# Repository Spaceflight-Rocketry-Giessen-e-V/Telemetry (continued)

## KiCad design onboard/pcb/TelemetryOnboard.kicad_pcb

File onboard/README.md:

# The Onboard System

- [Electronics Hardware](/onboard/pcb/)
    - [KiCad Design Files](/onboard/pcb/)
    - [PDF Schematic](/onboard/pcb/TelemetryOnboard_Schematic.pdf)
    - [Interactive Schematic / iBOM](/onboard/pcb/TelemetryOnboard_iBOM.html)
    - [BOM](/onboard/pcb/TelemetryOnboard_BOM.csv)
    - [Gerber Files](/onboard/pcb/Production%20Files/)
    - [PCB 3D Model](/onboard/pcb/TelemetryOnboard.step)
    - [PCB Images](/onboard/pcb/images/)
- [Mounting Structure](/onboard/mounting%20structure/)
- [Firmware](/onboard/firmware/)
- [869 MHz QFH Antenna](/onboard/antenna/) (not yet available)

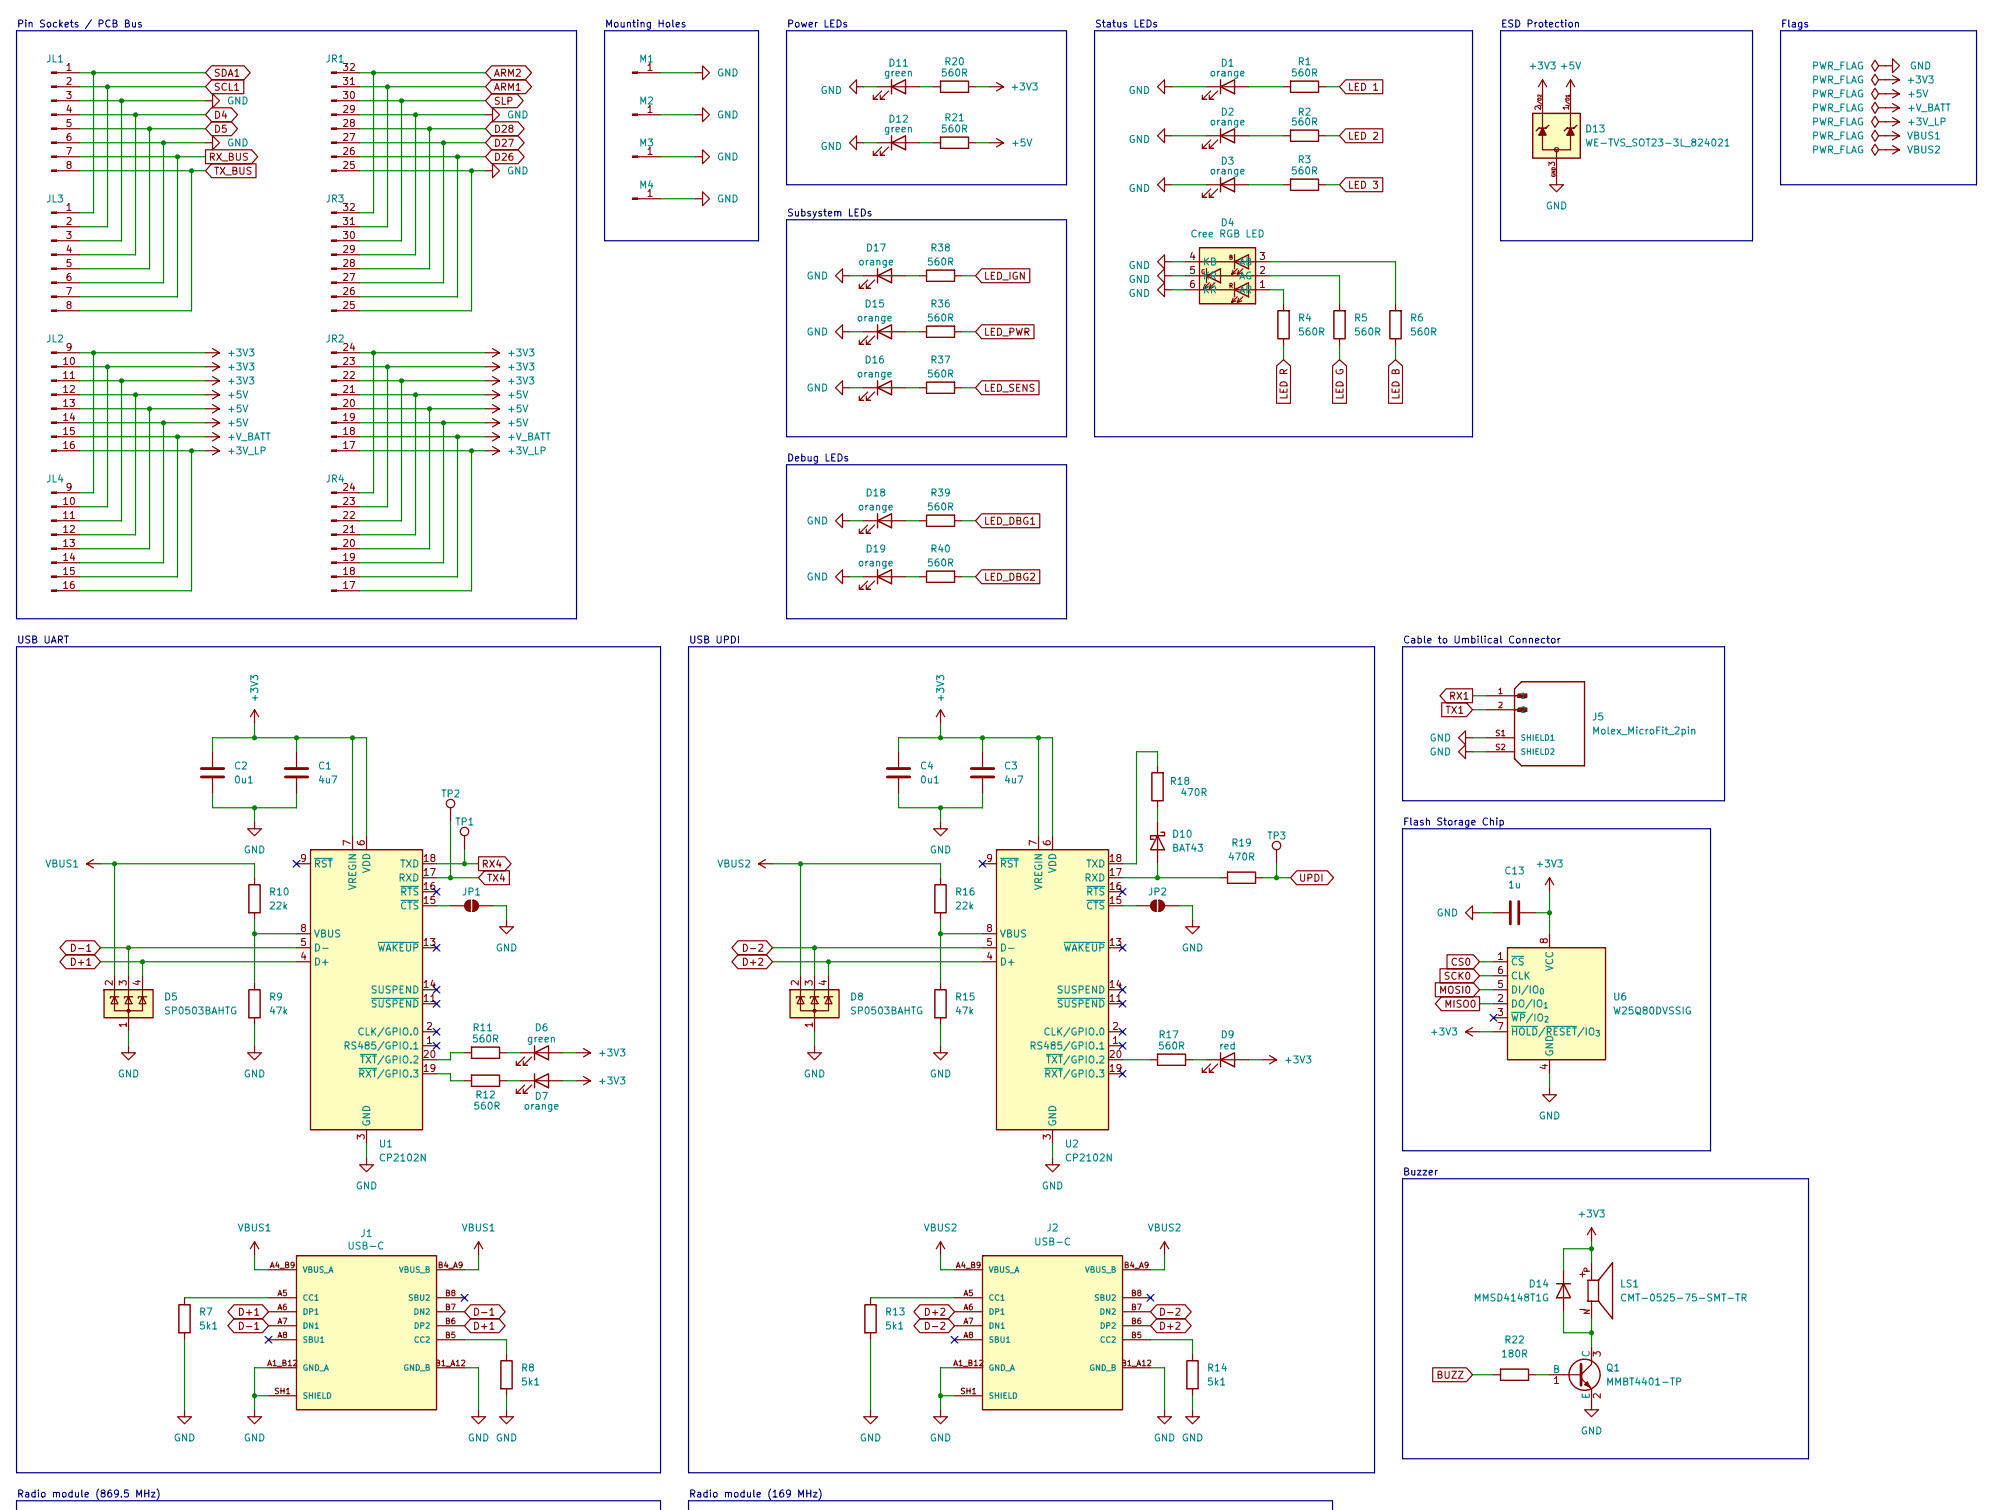
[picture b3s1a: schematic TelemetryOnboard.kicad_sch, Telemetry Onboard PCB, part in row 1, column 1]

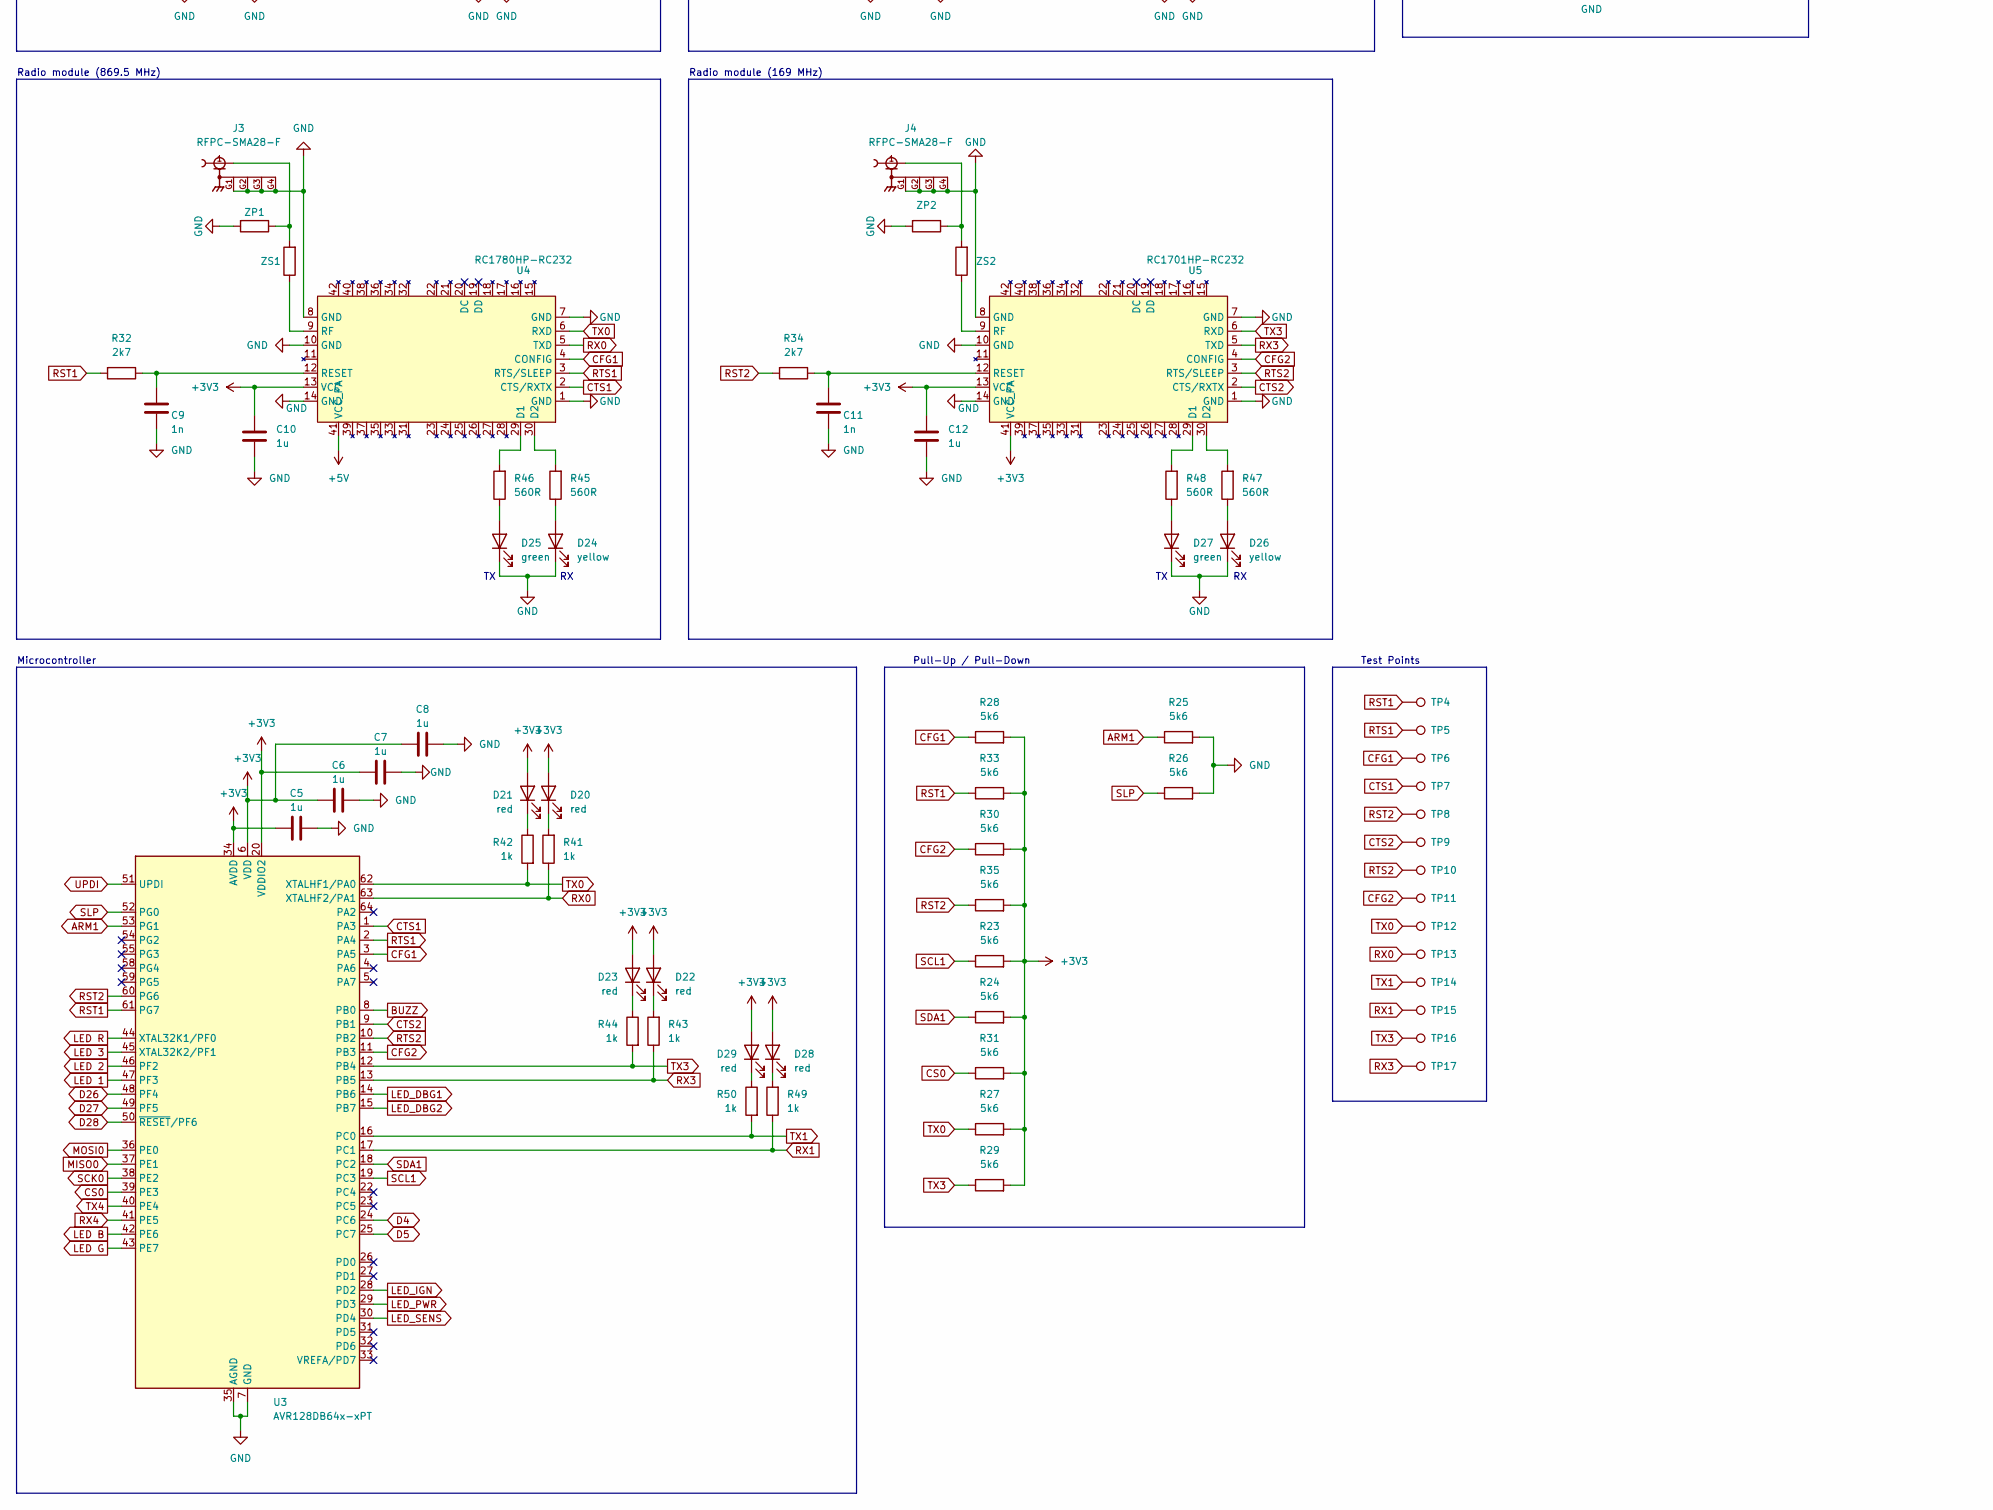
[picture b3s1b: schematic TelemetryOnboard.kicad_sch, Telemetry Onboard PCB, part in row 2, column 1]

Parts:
C1, C3: 4u7; C_0805_2012Metric_Pad1.18x1.45mm_HandSolder
C2, C4: 0u1; C_0805_2012Metric_Pad1.18x1.45mm_HandSolder
C5, C6, C7, C8, C10, C12, C13: 1u; C_0805_2012Metric_Pad1.18x1.45mm_HandSolder
C9, C11: 1n; C_0805_2012Metric_Pad1.18x1.45mm_HandSolder
D1, D2, D3, D7, D15, D16, D17, D18, D19: orange; LED_0805_2012Metric_Pad1.15x1.40mm_HandSolder
D4: Cree RGB LED
D5, D8: SP0503BAHTG; SOT-143
D6, D11, D12, D25, D27: green; LED_0805_2012Metric_Pad1.15x1.40mm_HandSolder
D9, D20, D21, D22, D23, D28, D29: red; LED_0805_2012Metric_Pad1.15x1.40mm_HandSolder
D10: BAT43; D_SOD-123
D13: WE-TVS_SOT23-3L_824021; SOT-23-3
D14: MMSD4148T1G; D_SOD-123
D24, D26: yellow; LED_0805_2012Metric_Pad1.15x1.40mm_HandSolder
J1, J2: USB-C; GCT_USB4216-03-A_REVA; PARTREV A; DigiKey_Part_Number 2073-USB4215-03-ACT-ND
J3, J4: RFPC-SMA28-F; PARTREV 1.0; DigiKey_Part_Number 2073-RFPC-SMA28-F-ND
J5: Molex_MicroFit_2pin; PARTREV F3; DigiKey_Part_Number WM1870-ND
JL1: Stackable Socket 1x8; JL1
JL2: Stackable Socket 1x8; JL2
JL3: Stackable Socket 1x8; JL3
JL4: Stackable Socket 1x8; JL4
JP1, JP2: SolderJumper_2_Open; Solder Jumper
JR1: Stackable Socket 1x8; JR1
JR2: Stackable Socket 1x8; JR2
JR3: Stackable Socket 1x8; JR3
JR4: Stackable Socket 1x8; JR4
LS1: CMT-0525-75-SMT-TR; Buzzer XDCR_CMT-0525-75-SMT-TR; PARTREV 1.0
M1, M2, M3, M4: M4 Mounting Hole
Q1: MMBT4401-TP; SOT-23
R1, R2, R3, R4, R5, R6, R11, R12, R17, R20, R21, R36, R37, R38, R39, R40, R45, R46, R47, R48: 560R; R_0805_2012Metric_Pad1.20x1.40mm_HandSolder
R7, R8, R13, R14: 5k1; R_0805_2012Metric_Pad1.20x1.40mm_HandSolder
R9, R15: 47k; R_0805_2012Metric_Pad1.20x1.40mm_HandSolder
R10, R16: 22k; R_0805_2012Metric_Pad1.20x1.40mm_HandSolder
R18, R19: 470R; R_0805_2012Metric_Pad1.20x1.40mm_HandSolder
R22: 180R; R_0805_2012Metric_Pad1.20x1.40mm_HandSolder
R23, R24, R25, R26, R27, R28, R29, R30, R31, R33, R35: 5k6; R_0805_2012Metric_Pad1.20x1.40mm_HandSolder
R32, R34: 2k7; R_0805_2012Metric_Pad1.20x1.40mm_HandSolder
R41, R42, R43, R44, R49, R50: 1k; R_0805_2012Metric_Pad1.20x1.40mm_HandSolder
TP1, TP2, TP3, TP4, TP5, TP6, TP7, TP8, TP9, TP10, TP11, TP12, TP13, TP14, TP15, TP16, TP17: TestPoint; Test Point
U1, U2: CP2102N; QFN20_CP2102N_SIL
U3: AVR128DB64x-xPT; TQFP-64_10x10mm_P0.5mm
U4: RC1780HP-RC232; Radiocrafts RC1780HP-RC232
U5: RC1701HP-RC232; Radiocrafts RC1780HP-RC232
U6: W25Q80DVSSIG; SOIC-8_5.3x5.3mm_P1.27mm
ZP1, ZP2: R_0805_2012Metric_Pad1.20x1.40mm_HandSolder
ZS1, ZS2: R_0805_2012Metric_Pad1.20x1.40mm_HandSolder

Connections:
+3V3: C1.1, C2.1, C3.1, C4.1, C5.1, C6.1, C7.2, C8.2, C10.1, C12.1, C13.2, D6.2 (A), D7.2 (A), D9.2 (A), D13.2, D14.1 (K), D20.2 (A), D21.2 (A), D22.2 (A), D23.2 (A), D28.2 (A), D29.2 (A), JL2.9 (Pin_1), JL2.10 (Pin_2), JL2.11 (Pin_3), JL4.9 (Pin_1), JL4.10 (Pin_2), JL4.11 (Pin_3), JR2.22 (26), JR2.23 (Pin_2), JR2.24 (Pin_1), JR4.22 (26), JR4.23 (Pin_2), JR4.24 (Pin_1), LS1.P, R20.1, R23.2, R24.2, R27.2, R28.2, R29.2, R30.2, R31.2, R33.2, R35.2, U1.6 (VDD), U1.7 (VREGIN), U2.6 (VDD), U2.7 (VREGIN), U3.6 (VDD), U3.20 (VDDIO2), U3.34 (AVDD), U3.56 (VDD), U4.13 (VCC), U5.13 (VCC), U5.41 (VCC_PA), U6.7 (~HOLD/~RESET/IO_{3}), U6.8 (VCC)
+3V_LP: JL2.16 (Pin_8), JL4.16 (Pin_8), JR2.17 (Pin_8), JR4.17 (Pin_8)
+5V: D13.1, JL2.12 (Pin_4), JL2.13 (Pin_5), JL2.14 (Pin_6), JL4.12 (Pin_4), JL4.13 (Pin_5), JL4.14 (Pin_6), JR2.19 (Pin_6), JR2.20 (Pin_5), JR2.21 (Pin_4), JR4.19 (Pin_6), JR4.20 (Pin_5), JR4.21 (Pin_4), R21.1, U4.41 (VCC_PA)
+V_BATT: JL2.15 (Pin_7), JL4.15 (Pin_7), JR2.18 (Pin_7), JR4.18 (Pin_7)
ARM1: JR1.31 (Pin_2), JR3.31 (Pin_2), R25.1, U3.53 (PG1)
ARM2: JR1.32 (Pin_1), JR3.32 (Pin_1)
BUZZ: R22.2, U3.8 (PB0)
CFG1: R28.1, TP6.1, U3.3 (PA5), U4.4 (CONFIG)
CFG2: R30.1, TP11.1, U3.11 (PB3), U5.4 (CONFIG)
CS0: R31.1, U3.39 (PE3), U6.1 (~CS)
CTS1: TP7.1, U3.1 (PA3), U4.2 (CTS/RXTX)
CTS2: TP9.1, U3.9 (PB1), U5.2 (CTS/RXTX)
D4: JL1.4, JL3.4, U3.24 (PC6)
D5: JL1.5, JL3.5, U3.25 (PC7)
D26: JR1.26 (Pin_7), JR3.26 (Pin_7), U3.48 (PF4)
D27: JR1.27 (Pin_6), JR3.27 (Pin_6), U3.49 (PF5)
D28: JR1.28 (Pin_5), JR3.28 (Pin_5), U3.50 (~RESET/PF6)
D+1: D5.4 (K), J1.A6 (DP1), J1.B6 (DP2), U1.4 (D+)
D+2: D8.4 (K), J2.A6 (DP1), J2.B6 (DP2), U2.4 (D+)
D-1: D5.3 (K), J1.A7 (DN1), J1.B7 (DN2), U1.5 (D-)
D-2: D8.3 (K), J2.A7 (DN1), J2.B7 (DN2), U2.5 (D-)
GND: C1.2, C2.2, C3.2, C4.2, C5.2, C6.2, C7.1, C8.1, C9.2, C10.2, C11.2, C12.2, C13.1, D1.1 (K), D2.1 (K), D3.1 (K), D4.4 (KB), D4.5 (KR), D4.6 (KR), D5.1 (A), D8.1 (A), D11.1 (K), D12.1 (K), D13.3, D15.1 (K), D16.1 (K), D17.1 (K), D18.1 (K), D19.1 (K), D24.1 (K), D25.1 (K), D26.1 (K), D27.1 (K), J1.A1_B12 (GND_A), J1.B1_A12 (GND_B), J1.SH1 (SHIELD), J1.SH2 (SHIELD), J1.SH3 (SHIELD), J1.SH4 (SHIELD), J2.A1_B12 (GND_A), J2.B1_A12 (GND_B), J2.SH1 (SHIELD), J2.SH2 (SHIELD), J2.SH3 (SHIELD), J2.SH4 (SHIELD), J3.G1, J3.G2, J3.G3, J3.G4, J4.G1, J4.G2, J4.G3, J4.G4, J5.S1 (SHIELD1), J5.S2 (SHIELD2), JL1.3, JL1.6, JL3.3, JL3.6, JP1.2 (B), JP2.2 (B), JR1.25 (Pin_8), JR1.29 (Pin_4), JR3.25 (Pin_8), JR3.29 (Pin_4), M1.1, M2.1, M3.1, M4.1, Q1.2 (E), R7.2, R8.2, R9.2, R13.2, R14.2, R15.2, R25.2, R26.2, U1.3 (GND), U1.12 (GND), U1.21 (GND), U2.3 (GND), U2.12 (GND), U2.21 (GND), U3.7 (GND), U3.21 (GND), U3.35 (AGND), U3.57 (GND), U4.1 (GND), U4.7 (GND), U4.8 (GND), U4.10 (GND), U4.14 (GND), U5.1 (GND), U5.7 (GND), U5.8 (GND), U5.10 (GND), U5.14 (GND), U6.4 (GND), ZP1.2, ZP2.2
LED 1: R1.1, U3.47 (PF3)
LED 2: R2.1, U3.46 (PF2)
LED 3: R3.1, U3.45 (XTAL32K2/PF1)
LED B: R6.1, U3.42 (PE6)
LED G: R5.1, U3.43 (PE7)
LED R: R4.1, U3.44 (XTAL32K1/PF0)
LED_DBG1: R39.2, U3.14 (PB6)
LED_DBG2: R40.2, U3.15 (PB7)
LED_IGN: R38.2, U3.28 (PD2)
LED_PWR: R36.2, U3.29 (PD3)
LED_SENS: R37.2, U3.30 (PD4)
MISO0: U3.37 (PE1), U6.2 (DO/IO_{1})
MOSI0: U3.36 (PE0), U6.5 (DI/IO_{0})
unnamed: D1.2 (A), R1.2
unnamed: D2.2 (A), R2.2
unnamed: D3.2 (A), R3.2
unnamed: D4.3 (AB), R6.2
unnamed: D4.2 (AG), R5.2
unnamed: D4.1 (AR), R4.2
unnamed: D6.1 (K), R11.1
unnamed: D7.1 (K), R12.1
unnamed: D9.1 (K), R17.1
unnamed: D10.2 (A), R19.2, U2.17 (RXD)
unnamed: D10.1 (K), R18.1
unnamed: D11.2 (A), R20.2
unnamed: D12.2 (A), R21.2
unnamed: D14.2 (A), LS1.N, Q1.3 (C)
unnamed: D15.2 (A), R36.1
unnamed: D16.2 (A), R37.1
unnamed: D17.2 (A), R38.1
unnamed: D18.2 (A), R39.1
unnamed: D19.2 (A), R40.1
unnamed: D20.1 (K), R41.2
unnamed: D21.1 (K), R42.1
unnamed: D22.1 (K), R43.2
unnamed: D23.1 (K), R44.1
unnamed: D24.2 (A), R45.1
unnamed: D25.2 (A), R46.1
unnamed: D26.2 (A), R47.1
unnamed: D27.2 (A), R48.1
unnamed: D28.1 (K), R49.2
unnamed: D29.1 (K), R50.1
unnamed: J1.A5 (CC1), R7.1
unnamed: J1.B5 (CC2), R8.1
unnamed: J2.A5 (CC1), R13.1
unnamed: J2.B5 (CC2), R14.1
unnamed: J3.1, ZP1.1, ZS1.2
unnamed: J4.1, ZP2.1, ZS2.2
unnamed: JP1.1 (A), U1.15 (~CTS)
unnamed: JP2.1 (A), U2.15 (~CTS)
unnamed: Q1.1 (B), R22.1
unnamed: R9.1, R10.2, U1.8 (VBUS)
unnamed: R12.2, U1.19 (~RXT/GPIO.3)
unnamed: R11.2, U1.20 (~TXT/GPIO.2)
unnamed: R18.2, U2.18 (TXD)
unnamed: R15.1, R16.2, U2.8 (VBUS)
unnamed: R17.2, U2.20 (~TXT/GPIO.2)
unnamed: R46.2, U4.29 (D1)
unnamed: R45.2, U4.30 (D2)
unnamed: C9.1, R32.1, U4.12 (RESET)
unnamed: U4.9 (RF), ZS1.1
unnamed: R48.2, U5.29 (D1)
unnamed: R47.2, U5.30 (D2)
unnamed: C11.1, R34.1, U5.12 (RESET)
unnamed: U5.9 (RF), ZS2.1
RST1: R32.2, R33.1, TP4.1, U3.61 (PG7)
RST2: R34.2, R35.1, TP8.1, U3.60 (PG6)
RTS1: TP5.1, U3.2 (PA4), U4.3 (RTS/SLEEP)
RTS2: TP10.1, U3.10 (PB2), U5.3 (RTS/SLEEP)
RX0: R41.1, TP13.1, U3.63 (XTALHF2/PA1), U4.5 (TXD)
RX1: J5.1, R49.1, TP15.1, U3.17 (PC1)
RX3: R43.1, TP17.1, U3.13 (PB5), U5.5 (TXD)
RX4: TP1.1, U1.18 (TXD), U3.41 (PE5)
RX_BUS: JL1.7, JL3.7
SCK0: U3.38 (PE2), U6.6 (CLK)
SCL1: JL1.2, JL3.2, R23.1, U3.19 (PC3)
SDA1: JL1.1, JL3.1, R24.1, U3.18 (PC2)
SLP: JR1.30 (26), JR3.30 (26), R26.1, U3.52 (PG0)
TX0: R27.1, R42.2, TP12.1, U3.62 (XTALHF1/PA0), U4.6 (RXD)
TX1: J5.2, R50.2, TP14.1, U3.16 (PC0)
TX3: R29.1, R44.2, TP16.1, U3.12 (PB4), U5.6 (RXD)
TX4: TP2.1, U1.17 (RXD), U3.40 (PE4)
TX_BUS: JL1.8, JL3.8
UPDI: R19.1, TP3.1, U3.51 (UPDI)
VBUS1: D5.2 (K), J1.A4_B9 (VBUS_A), J1.B4_A9 (VBUS_B), R10.1
VBUS2: D8.2 (K), J2.A4_B9 (VBUS_A), J2.B4_A9 (VBUS_B), R16.1

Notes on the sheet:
Subsystem LEDs
Pull-Up / Pull-Down
Pin Sockets / PCB Bus
Flash Storage Chip
Microcontroller
Radio module (169 MHz)
Flags
USB UPDI
Test Points
Buzzer
USB UART
Status LEDs
Debug LEDs
Mounting Holes
Power LEDs
ESD Protection
Radio module (869.5 MHz)
Cable to Umbilical Connector

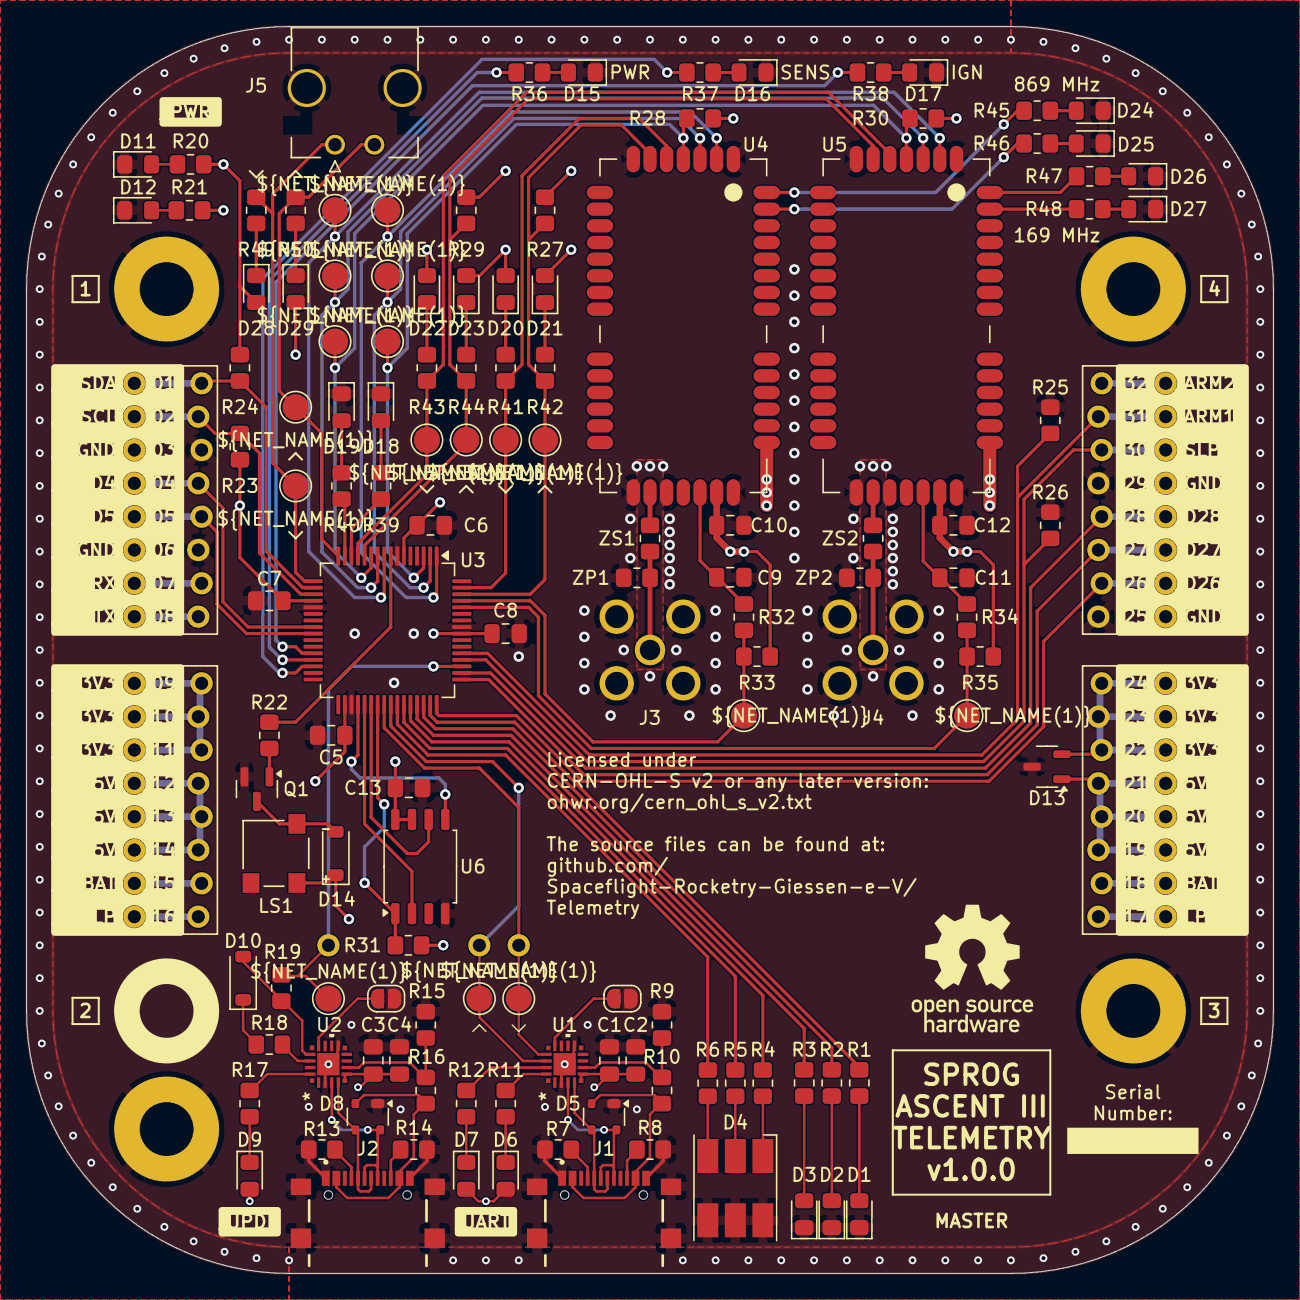
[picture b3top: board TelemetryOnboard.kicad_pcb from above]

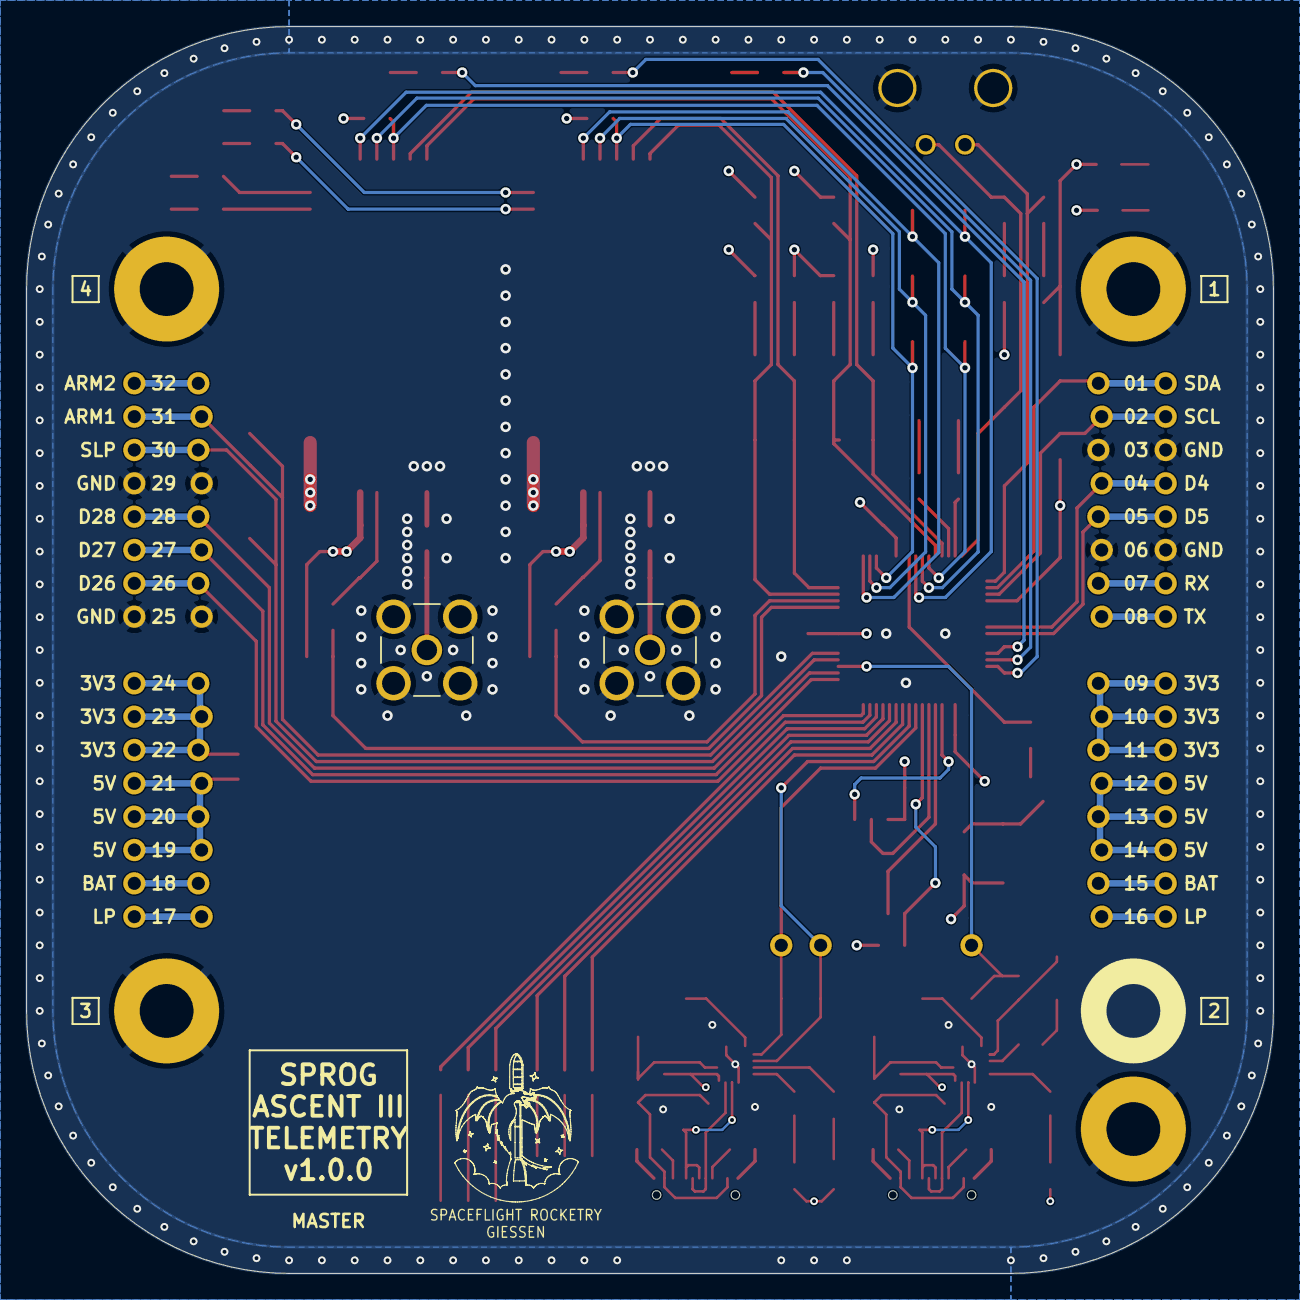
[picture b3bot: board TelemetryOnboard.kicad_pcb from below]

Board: 4 copper layers, 95.0 x 95.0 mm, 140 parts (2 on the bottom side), 108 nets.

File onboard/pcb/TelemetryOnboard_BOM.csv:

"Reference","Qty","Value","Footprint","DNP","Purchase-URL"
"C1,C3","2","4u7","Capacitor_SMD:C_0805_2012Metric_Pad1.18x1.45mm_HandSolder","","https://www.digikey.de/de/products/detail/samsung-electro-me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"
"C2,C4","2","0u1","Capacitor_SMD:C_0805_2012Metric_Pad1.18x1.45mm_HandSolder","","https://www.digikey.de/de/products/detail/samsung-electro-me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"
"C5,C6,C7,C8,C10,C12,C13","7","1u","Capacitor_SMD:C_0805_2012Metric_Pad1.18x1.45mm_HandSolder","","https://www.digikey.de/de/products/detail/samsung-electro-me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"
"C9,C11","2","1n","Capacitor_SMD:C_0805_2012Metric_Pad1.18x1.45mm_HandSolder","","https://www.digikey.de/de/products/detail/samsung-electro-me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"
"D1,D2,D3,D7,D15,D16,D17,D18,D19","9","orange","LED_SMD:LED_0805_2012Metric_Pad1.15x1.40mm_HandSolder","","https://www.digikey.de/de/products/detail/liteon/LTST-C170KF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"
"D4","1","Cree RGB LED","Footprints:Cree RGB LED","","https://www.digikey.de/de/products/detail/cree-led/CLP6C-FKB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"
"D5,D8","2","SP0503BAHTG","Package_TO_SOT_SMD:SOT-143","","https://www.digikey.de/de/products/detail/littelfuse-inc/SP0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"
"D6,D11,D12,D25,D27","5","green","LED_SMD:LED_0805_2012Metric_Pad1.15x1.40mm_HandSolder","","https://www.digikey.de/de/products/detail/liteon/LTST-C171KG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"
"D9,D20,D21,D22,D23,D28,D29","7","red","LED_SMD:LED_0805_2012Metric_Pad1.15x1.40mm_HandSolder","","https://www.digikey.de/de/products/detail/liteon/LTST-C171KR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"
"D10","1","BAT43","Diode_SMD:D_SOD-123","","https://www.digikey.de/de/products/detail/mcc-micro-commerci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"
"D13","1","WE-TVS_SOT23-3L_824021","Package_TO_SOT_SMD:SOT-23-3","","https://www.digikey.de/de/products/detail/w%C3%BCrth-elektro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"
"D14","1","MMSD4148T1G","Diode_SMD:D_SOD-123","","https://www.digikey.de/de/products/detail/onsemi/MMSD4148T1G/919705"
"D24,D26","2","yellow","LED_SMD:LED_0805_2012Metric_Pad1.15x1.40mm_HandSolder","","https://www.digikey.de/de/products/detail/liteon/LTST-C170KS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"
"J1,J2","2","USB-C","Footprints:GCT_USB4216-03-A_REVA","","https://www.digikey.de/de/products/detail/gct/USB4216-03-A/26598207"
"J3,J4","2","RFPC-SMA28-F","Footprints:RFPC-SMA28-F","","https://www.digikey.de/de/products/detail/gct/RFPC-SMA28-F/2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"
"J5","1","Molex_MicroFit_2pin","Footprints:Molex_MicroFit_2pin","","https://www.digikey.de/de/products/detail/molex/0436500203/268999"
"JL1,JL2,JL3,JL4","4","Stackable Socket 1x8","Footprints:JL1,Footprints:JL2,Footprints:JL3,Footprints:JL4","","https://www.digikey.de/de/products/detail/samtec-inc/ESQ-108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,~"
"JR1,JR2,JR3,JR4","4","Stackable Socket 1x8","Footprints:JR1,Footprints:JR2,Footprints:JR3,Footprints:JR4","","https://www.digikey.de/de/products/detail/samtec-inc/ESQ-108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,~"
"LS1","1","CMT-0525-75-SMT-TR","Footprints:Buzzer XDCR_CMT-0525-75-SMT-TR","","https://www.digikey.de/de/products/detail/same-sky-formerly-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"
"M1,M2,M3,M4","4","M4 Mounting Hole","Footprints:M4 Mounting Hole","","~"
"Q1","1","MMBT4401-TP","Package_TO_SOT_SMD:SOT-23","","https://www.digikey.de/de/products/detail/mcc-micro-commerci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"
"R1,R2,R3,R4,R5,R6,R11,R12,R17,R20,R21,R36,R37,R38,R39,R40,R45,R46,R47,R48","20","560R","Resistor_SMD:R_0805_2012Metric_Pad1.20x1.40mm_HandSolder","","https://www.digikey.de/de/products/detail/stackpole-electron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"
"R7,R8,R13,R14","4","5k1","Resistor_SMD:R_0805_2012Metric_Pad1.20x1.40mm_HandSolder","","https://www.digikey.de/de/products/detail/stackpole-electron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"
"R9,R15","2","47k","Resistor_SMD:R_0805_2012Metric_Pad1.20x1.40mm_HandSolder","","https://www.digikey.de/de/products/detail/stackpole-electron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"
"R10,R16","2","22k","Resistor_SMD:R_0805_2012Metric_Pad1.20x1.40mm_HandSolder","","https://www.digikey.de/de/products/detail/stackpole-electron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"
"R18,R19","2","470R","Resistor_SMD:R_0805_2012Metric_Pad1.20x1.40mm_HandSolder","","https://www.digikey.de/de/products/detail/stackpole-electron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"
"R22","1","180R","Resistor_SMD:R_0805_2012Metric_Pad1.20x1.40mm_HandSolder","","https://www.digikey.de/de/products/detail/stackpole-electron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"
"R23,R24,R25,R26,R27,R28,R29,R30,R31,R33,R35","11","5k6","Resistor_SMD:R_0805_2012Metric_Pad1.20x1.40mm_HandSolder","","https://www.digikey.de/de/products/detail/stackpole-electron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"
"R32,R34","2","2k7","Resistor_SMD:R_0805_2012Metric_Pad1.20x1.40mm_HandSolder","","https://www.digikey.de/de/products/detail/stackpole-electron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"
"R41,R42,R43,R44,R49,R50","6","1k","Resistor_SMD:R_0805_2012Metric_Pad1.20x1.40mm_HandSolder","","https://www.digikey.de/de/products/detail/stackpole-electron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"
"TP1,TP2,TP3,TP4,TP5,TP6,TP7,TP8,TP9,TP10,TP11,TP12,TP13,TP14,TP15,TP16,TP17","17","TestPoint","Footprints:Test Point","","~"
"U1,U2","2","CP2102N","Footprints:QFN20_CP2102N_SIL","","https://www.digikey.de/de/products/detail/silicon-labs/CP210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"
"U3","1","AVR128DB64x-xPT","Package_QFP:TQFP-64_10x10mm_P0.5mm","","https://www.digikey.de/de/products/detail/microchip-technolo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"
"U4","1","RC1780HP-RC232","Footprints:Radiocrafts RC1780HP-RC232","","https://www.digikey.de/de/products/detail/radiocrafts-as/RC1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"
"U5","1","RC1701HP-RC232","Footprints:Radiocrafts RC1780HP-RC232","","https://www.digikey.de/de/products/detail/radiocrafts-as/RC1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"
"U6","1","W25Q80DVSSIG","Package_SO:SOIC-8_5.3x5.3mm_P1.27mm","","https://www.digikey.de/de/products/detail/winbond-electronic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"
"ZP1,ZP2","2","~","Resistor_SMD:R_0805_2012Metric_Pad1.20x1.40mm_HandSolder","","~"
"ZS1,ZS2","2","~","Resistor_SMD:R_0805_2012Metric_Pad1.20x1.40mm_HandSolder","","~"

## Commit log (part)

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2025-10-19 add better simulation with csv IO
    update simulation with more realistic values and add io support for csv flight data files
2025-10-25 update cobs value range
2025-10-26 Update image path in system overview documentation
2025-11-03 update packet library dependency
2025-11-10 update to onboard firmware
    fix to i2c comm bugs and more
2025-11-17 update to files before going public
2025-11-21 update to manual
2025-11-21 update radio commands
2025-11-24 Update firmware groundstation
2025-11-24 update to ground station firmware
2025-11-26 Flight Simulator: Upload example flight data
2025-11-26 Move Flight Simulator to a new repo (Flight-Simulations)
    Move Flight Simulator to a new repo:
    https://github.com/Spaceflight-Rocketry-Giessen-e-V/Flight-Simulations
2025-11-30 add readme and requirements to linkbudget simulation. fixes #14
2025-12-03 Change COM monitor from binary to ASCII display
2025-12-07 change view to plain and remove old setting file
2025-12-08 add interactive bom
2025-12-10 Ignore telemetry log files and remove tracked logs
    Added telemetry log files and Python cache files to .gitignore to prevent them from being tracked. Deleted existing telemetry_log.csv and telemetry_log.txt from the repository.
2025-12-10 Add accelerometer window and enhance UI modularity
    Introduces a new AccelerometerWindow with a graphical g-force indicator. Refactors all window draw_ui methods to accept size parameters for improved layout flexibility. Updates the Arduino simulation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
2025-12-11 add parachute deployment capability and parity check
    fixes #10
2025-12-11 add more documentation for handling the groundstation
2025-12-14 change main deployment behaviour
2025-12-27 add documentation to packet lib
    fixes #8
2025-12-28 change order of the documentation
2025-12-28 move antenna meas. theory to user manual
2026-01-04 Meerkat: Fix images
2026-01-08 improve documentation
    added documentation text and images and informations about versioning
2026-01-14 fix firmware bug
2026-01-26 update linkbudget simulation
    upgrade to more realistic flight profile based on elapsed time instead of height
2026-01-26 include updi programmer circuit
2026-02-02 first version new schematic
    added symbols, footprints, 3dmodels, added new pcb base layout, added first schematic elements
2026-02-05 update platine
2026-02-06 Led resistor from 270 to 560+
2026-02-11 add Groundstation Motherboard
2026-02-11 add Daugther board schematic
2026-02-11 change esd prot name
2026-02-12 include electronics photograph
2026-02-18 change gitignore settings
2026-02-18 include input from ignition system
2026-02-19 started daughterboard pcb design
2026-02-22 place other components on pcb
2026-02-25 small change
2026-02-25 change dim to 40x70
2026-02-27 finalized design of daughterbaord
2026-02-27 add motherboard pcb
2026-02-28 improve DB silkscreen and edge cuts
2026-03-01 Fix latex bug
2026-03-01 update coplanar waveguid calculation
    fixes #28. Added separate caluclations for groundstation and onboard and updates the values
2026-03-04 add power supply via USB to Motherboard
2026-03-07 add purchase links to components
2026-03-08 finishing touches to motherboard
2026-03-19 generate files for merge with main
2026-03-19 added file to be merged
2026-03-19 improve manual structure and add cp2102n manual
    include manual for programming the leds connected to the cp2102n usb-to-uart bridge. fixes #25
2026-03-21 inluce kicad custom libraries manual
    fixes #19
2026-03-22 include new pcb renderings
2026-03-28 update code for new groundstation pcb Fixes #33
2026-03-30 add drawing sheet informations
2026-04-06 include changes since last version in january
    fixes #34
2026-04-11 Move linkbudget simulation to common/linkbudget
    Rename/move linkbudget simulation files from simulations/linkbudget to common/linkbudget
    Fixes #41
2026-04-11 Update antenna assembly mask image
2026-04-11 complete repo restructuring and fix linking issues
2026-04-12 update helix antenna assembly manual
    rework text, downsize images and more
2026-04-15 improve user manual
    include simplicity studio project creation and improve structure
2026-04-16 Add run.bat; plotting controls & UI fixes
    Add a Windows run.bat to create/activate venv, install requirements and launch main.py.
    Update UI: remove emoji from Settings tab label and fix swapped altitude update calls in ui_manager (GNSS vs pressure).
    Enhance AccelerationWindow and AltitudeWindow with Stop/Resume and Reset Plot buttons, implement resume/reset logic, adjust layout and tags, and remove per-sample delta/median tracking from altitude 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
    Fix MapViewWindow GPS validity check to use the local lat/lon parameters instead of self members.
2026-04-25 include radiocrafts in library name
2026-04-25 include new improved renderin
2026-04-26 improve gitignore scope
2026-05-07 exclude html and bat from languages
2026-05-08 Add VGA cable specification user_manual.md
2026-05-09 Add antennas simulation to user_manual.md
    fixes #21
2026-05-15 Update Motherboard Pin Initialisations
2026-05-20 small update
    advances with #17 and #18
2026-05-26 Update helix_antenna_assembly_manual.md with centered pictures
2026-05-27 create rough firmware outline
    fixes #49 fixes #50 Co-Authored-By: BenjaminBBBBBB <benjamin.bauersfeld@t-online> Co-Authored-By: Abakus2k <mail@pascalschlag.de> Co-Authored-By: Niklas-2911 <niklas_ow@proton.me>
2026-05-31 Docs: Add GUI overview, remove images from deprecated version
    Add a comprehensive GUI section to docs, remove old images form prior gui versions
2026-05-31 add function definitions to header files and main
    fixes #47 fixes #48
2026-06-02 Revise CHANGELOG format and add new entries
    Updated the CHANGELOG format and added new entries for unreleased features and changes.
2026-06-02 Restructure antenna folder: split into helical/ and add patch antenna
    groundstation/antenna/ now holds one subfolder per antenna design:
    - helical/: the existing 869 MHz helical antenna (moved unchanged)
    - patch/: new RHCP patch antenna simulation source imported from the
    standalone PatchAntennaSimulation project (source only: config.py,
    run.py, requirements.txt, src/*.py), with a scoped .gitignore for the
    regenerable openEMS/FDTD run output.
2026-06-03 Refactor patch antenna optimizer: share metrics, remove dead code, fix logic
    Structural cleanup (no change to simulation physics or exported PCB geometry):
    - Extract shared S11 / axial-ratio / centroid / eval-grid / failure-result
    helpers into new src/metrics.py, used by both the optimizer worker and the
    post-processor (removes copy-pasted numeric logic across three files).
    - Delete the dead _run_single method and its now-unused shutil/tempfile imports.
    - Drop the never-enabled _dbg tracer from build_sim.
2026-06-03 @ Patch antenna optimizer: parallelization fixes and grid tuning
    - Reuse one ProcessPoolExecutor across all phases instead of rebuilding it
    per phase, avoiding 7x worker respawn + openEMS re-import on Windows spawn.
    - Control openEMS threads via Run(numThreads=...): workers get their dynamic
    share of cores (immune to inherited OMP_NUM_THREADS, which setdefault left
    unenforced), the final/single sim claims all cores, and under-filled waves
    hand idle cores to the running sims.
2026-06-03 Patch optimizer: GP area penalty, band-worst AR selection, convergence bump
    Stop the optimiser inflating the ground plane and being fooled by a
    single-frequency axial-ratio reading.
    - config: add W_AREA area penalty and cap the Phase-4 GP sweep to a
    110-170 mm board (was 200-400 mm) -- gain saturates past ~0.6 lambda,
    so a bigger board just adds cost.
    - _cost: add board-area penalty (proportional to sub_hw^2) so Phase 4
2026-06-05 add send functions
2026-06-05 small changes
2026-06-05 Fix formatting
2026-06-05 Add radioModuleConfigure, commandReceive
    Add radioModuleSetup, radioModuleConfigure
    Add commandReceive
2026-06-07 Patch antenna: simulation & optimizer pipeline
    openEMS/FDTD model of the flat dual-feed (branch-line coupler) RHCP patch at 869.525 MHz on NP-140F (er 4.15), 160 mm ground plane for wide beamwidth. Covers geometry build, model, optimizer, coverag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
2026-06-07 Patch antenna: research docs & BOM
    Design research notes, migration plan, and bill of materials for the flat dual-feed branch-line-coupler patch, plus WIP status.
2026-06-07 Patch antenna: refresh WIP status to current validated state
    Sync the headline metrics to the latest sim (S11 -11.0 dB, AR 1.64 dB, Dmax 3.9 dBi, AR<=3 beam 56 deg) and add the 45 deg coverage-cone figures (worst AR 5.3 dB, min RHCP gain ~0 dBic). Update the e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
2026-06-08 Patch antenna: recentre W optimiser grid on measured resonance + retire dual-feed BOM/plan
    Pre-optimise review of the single-feed pipeline (geometry/code/design):
    - Optimiser W grid was symmetric about the seed (0.98/1.00/1.02), but the 150k
    confirmation run measured the W=82.5 seed at 875.4 MHz (+5.9 high). Resonance
    must come DOWN, i.e. W must grow; the AR null tracks resonance, so the symmetric
    grid would just reproduce AR ~4.8 dB at f_target. Recentre GRID_W_FRAC to
    (1.0000, 1.0067, 1.0133) so the predicted on-resonance W (x 875.4/869.525) sits
2026-06-08 Patch antenna: harden AR-null optimiser per adversarial review
    Adversarial multi-agent review of the AR-null fix confirmed one bug and surfaced cheap
    consistency hardening (the verified-not-real findings are addressed too as they are low-risk):
    - optimizer: per-phase hang guard now scales with the actual per-host work
    (max(PHASE_TIMEOUT_S, 4x waves x per-sim)), not a fixed 3 h calibrated to the 20-thread
    reference host - a slow/few-core box running 3 serial 150k waves was wrongly marked a
    timeout failure. [confirmed bug]
2026-06-08 Patch antenna: guard against empty NF2FF (zero far-field) in the optimiser worker
    The verification optimise exposed a resource limit: 9 concurrent sims at NrTS=150k returned
    EMPTY NF2FF (Prad~0, Dmax~0, AR=-inf) while the port S11 stayed valid - the openEMS NF2FF
    recording scales with NrTS and 9x150k apparently overran RAM/temp-disk (9x60k and 3x150k
    both worked). Those garbage sims returned ok=True with a finite cost (-1.20), which would
    silently pollute grid selection.
    The worker now validates res_f.Prad>0 and Dmax>0; otherwise it returns a failure_result
2026-06-08 Patch antenna: record eps sweep result (CP eps-fragile, only nominal passes)
2026-06-08 Patch antenna: silk layout - QR right of patch, description top, logos centred-left; remove back graph + resistor text
2026-06-08 Patch antenna: move Patch/trunc labels to under the patch (left of the feed)
2026-06-10 small typo in Packet.cpp with unint8_t
2026-06-10 Add led class and button class for the motherboard
2026-06-11 add encode, decode frame functions
    packet framing: cobs, parity, packet identifier, end byte
2026-06-12 Add coding funktions for flightData
2026-06-13 rework onboard firmware to fix several bugs
2026-06-29 remove images from radiocrafts datasheets
    replace with table
